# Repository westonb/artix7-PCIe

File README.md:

# artix7-PCIe
Originally designed for a SDR expansion card. Design includes breakout header, 2 general purpose buttons, and a SFP cage. 

Optimized for OSHPark 4 layer fab and home assembly. 

Design has been built but prototypes were killed by JTAG ground loop due to user error. Further work not certain, but please fork and feel free to contact for support.

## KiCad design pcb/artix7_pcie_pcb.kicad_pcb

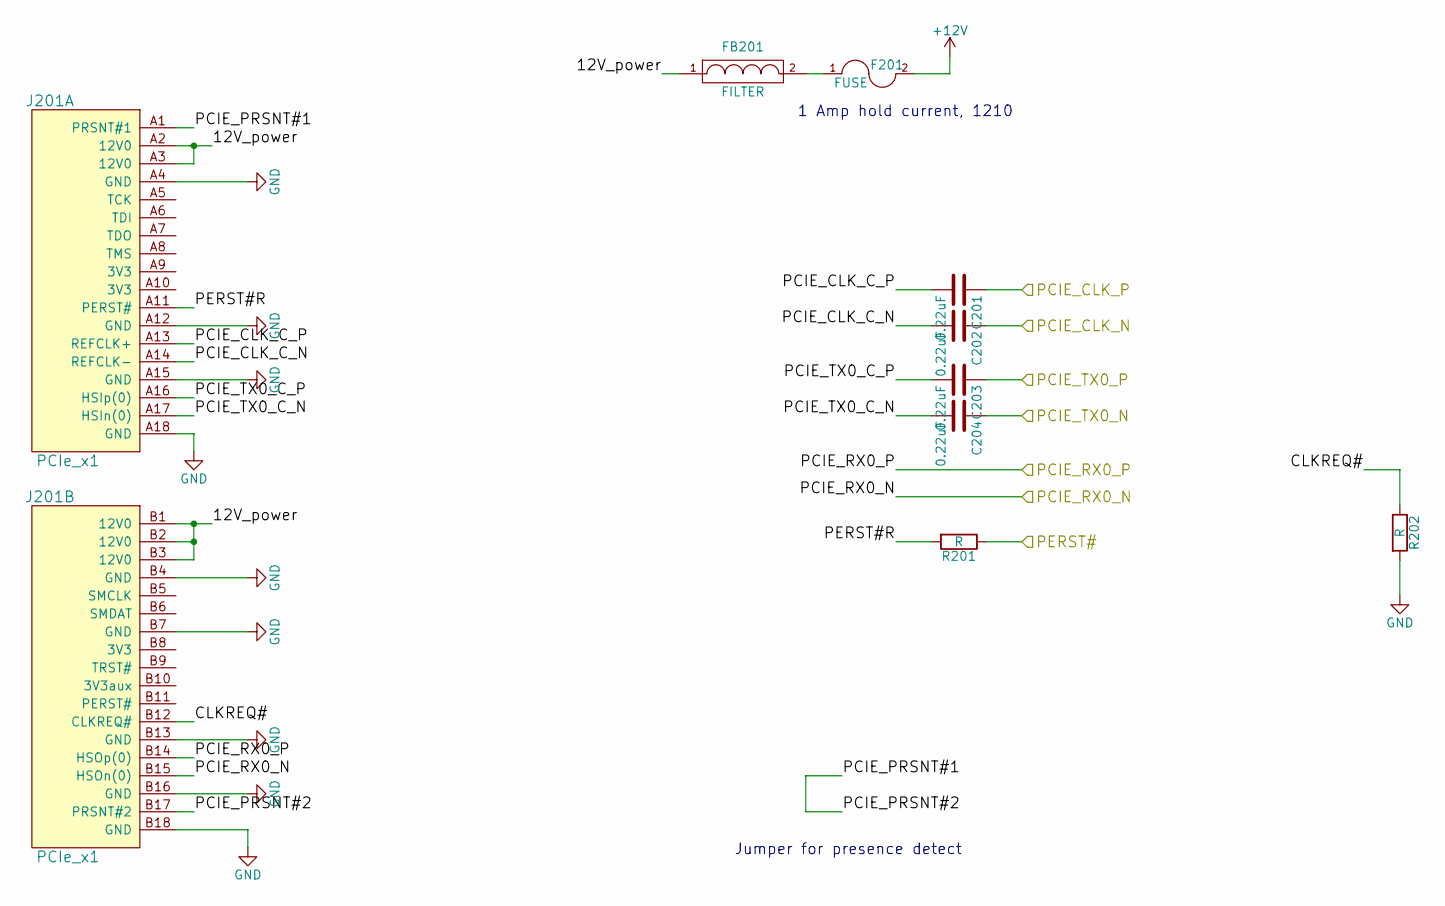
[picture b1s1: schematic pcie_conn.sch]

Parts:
C201, C202, C203, C204: 0.22uF; C_0402
F201: FUSE; SMD-0805
FB201: FILTER; L_0603
J201: PCIe_x1; PCIe_1x
R201, R202: R; R_0402

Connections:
+12V: F201.2; also elsewhere on the board
/FPGA Transceivers/PCIE_CLK_N: C202.1; also elsewhere on the board
/FPGA Transceivers/PCIE_CLK_P: C201.1; also elsewhere on the board
/FPGA Transceivers/PCIE_RX0_N: J201.B15 (HSOn(0)); also elsewhere on the board
/FPGA Transceivers/PCIE_RX0_P: J201.B14 (HSOp(0)); also elsewhere on the board
/FPGA Transceivers/PCIE_TX0_N: C204.1; also elsewhere on the board
/FPGA Transceivers/PCIE_TX0_P: C203.1; also elsewhere on the board
/PCIe Connector/12V_power: FB201.1, J201.A2 (12V0), J201.A3 (12V0), J201.B1 (12V0), J201.B2 (12V0), J201.B3 (12V0)
/PCIe Connector/CLKREQ#: J201.B12 (CLKREQ#), R202.1
/PCIe Connector/PCIE_CLK_C_N: C202.2, J201.A14 (REFCLK-)
/PCIe Connector/PCIE_CLK_C_P: C201.2, J201.A13 (REFCLK+)
/PCIe Connector/PCIE_PRSNT#1: J201.A1 (PRSNT#1), J201.B17 (PRSNT#2)
/PCIe Connector/PCIE_TX0_C_N: C204.2, J201.A17 (HSIn(0))
/PCIe Connector/PCIE_TX0_C_P: C203.2, J201.A16 (HSIp(0))
/PCIe Connector/PERST#R: J201.A11 (PERST#), R201.2
/User IO/PCIE_PERST: R201.1; also elsewhere on the board
GND: J201.A4 (GND), J201.A12 (GND), J201.A15 (GND), J201.A18 (GND), J201.B4 (GND), J201.B7 (GND), J201.B13 (GND), J201.B16 (GND), J201.B18 (GND), R202.2; also elsewhere on the board
unnamed: F201.1, FB201.2

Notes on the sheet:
Jumper for presence detect
1 Amp hold current, 1210

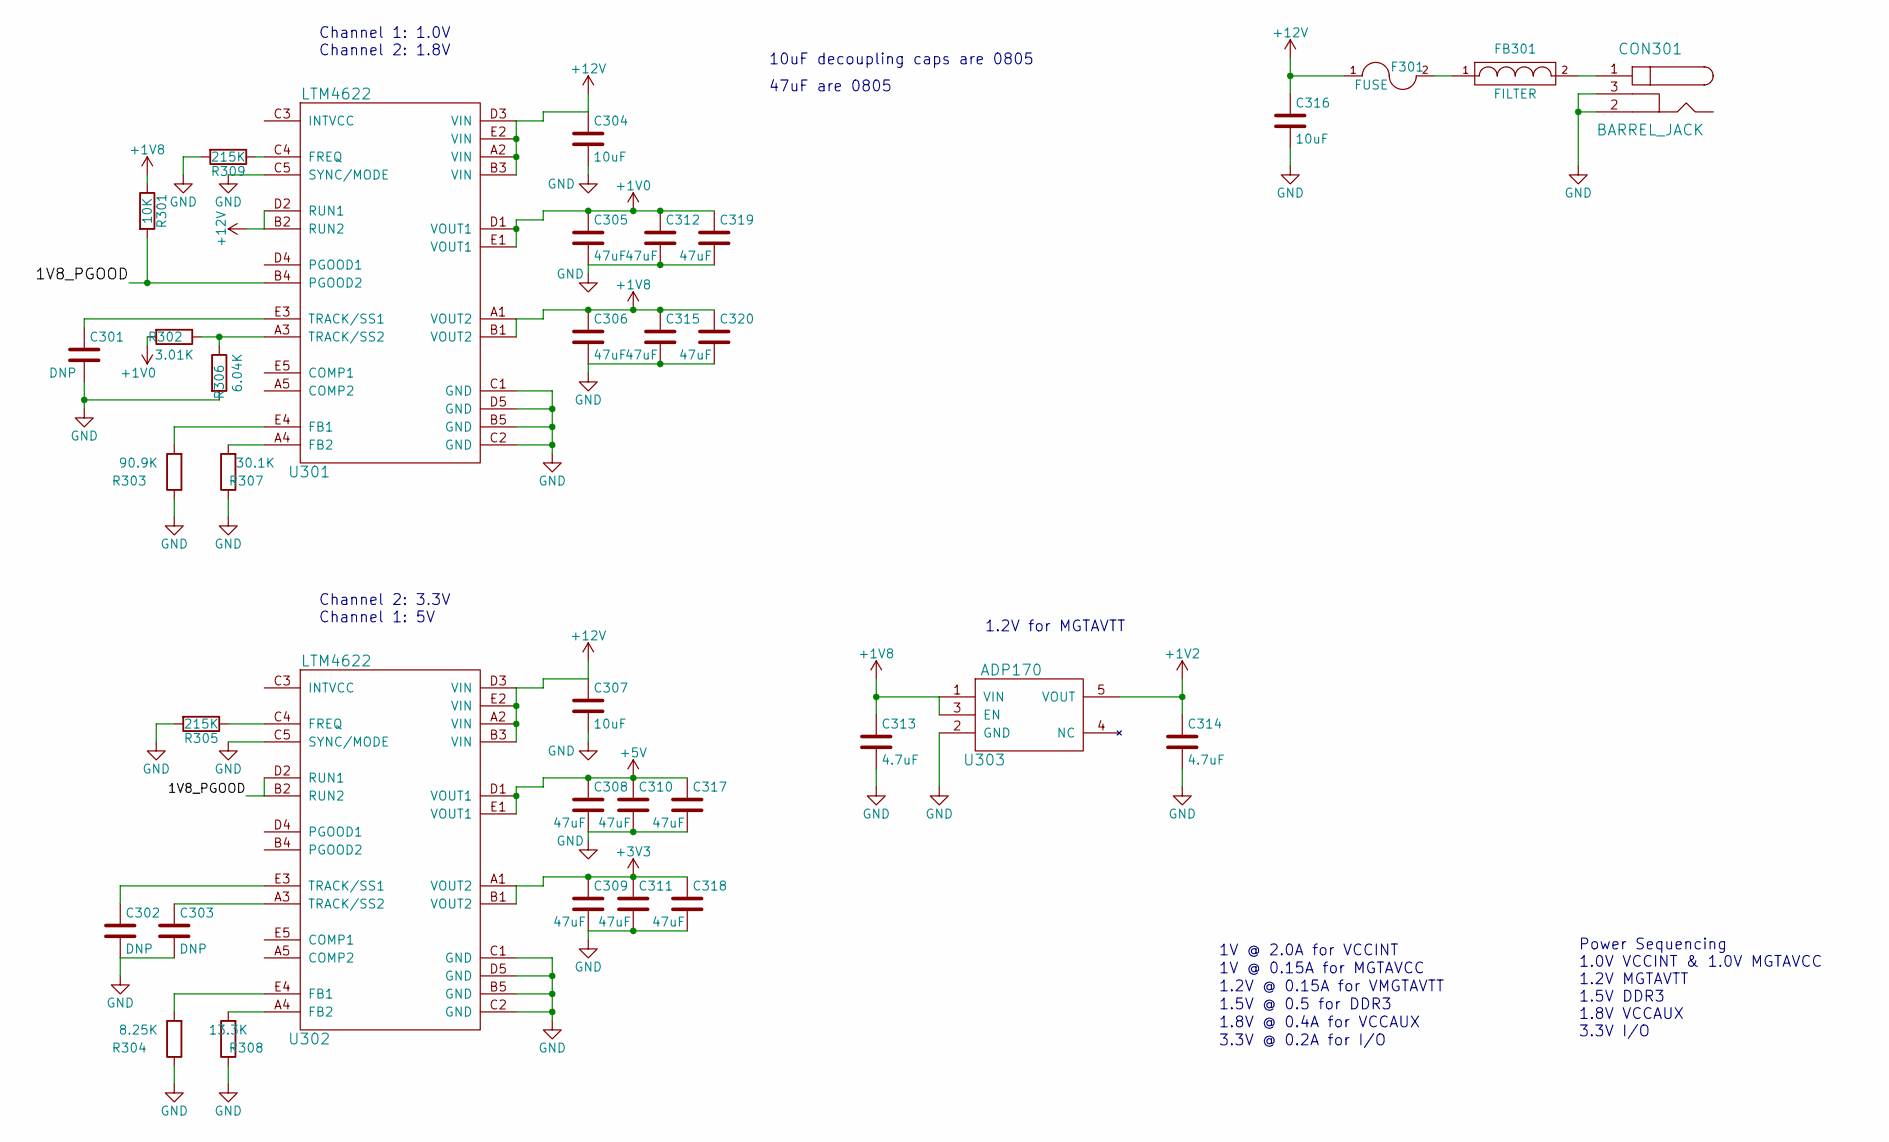
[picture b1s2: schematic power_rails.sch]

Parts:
C301, C302, C303: DNP; C_0402
C304, C307, C316: 10uF; C_0805
C305, C306, C308, C309, C310, C311, C312, C315, C317, C318, C319, C320: 47uF; C_0805
C313, C314: 4.7uF; C_0402
CON301: BARREL_JACK; DC_2.1mm_PJ-202A
F301: FUSE; SMD-0805
FB301: FILTER; L_0603
R301: 10K; R_0402
R302: 3.01K; R_0402
R303: 90.9K; R_0402
R304: 8.25K; R_0402
R305, R309: 215K; R_0402
R306: 6.04K; R_0402
R307: 30.1K; R_0402
R308: 13.3K; R_0402
U301, U302: LTM4622; LGA25_6_25x6_25
U303: ADP170; TSOT-23-5

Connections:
+1V0: C305.1, C312.1, C319.1, R302.2, U301.D1 (VOUT1), U301.E1 (VOUT1); also elsewhere on the board
+1V2: C314.1, U303.5 (VOUT); also elsewhere on the board
+1V8: C306.1, C313.1, C315.1, C320.1, R301.1, U301.A1 (VOUT2), U301.B1 (VOUT2), U303.1 (VIN), U303.3 (EN); also elsewhere on the board
+3V3: C309.1, C311.1, C318.1, U302.A1 (VOUT2), U302.B1 (VOUT2); also elsewhere on the board
+5V: C308.1, C310.1, C317.1, U302.D1 (VOUT1), U302.E1 (VOUT1); also elsewhere on the board
+12V: C304.1, C307.1, C316.1, F301.1, U301.A2 (VIN), U301.B2 (RUN2), U301.B3 (VIN), U301.D2 (RUN1), U301.D3 (VIN), U301.E2 (VIN), U302.A2 (VIN), U302.B3 (VIN), U302.D3 (VIN), U302.E2 (VIN); also elsewhere on the board
/Power Rails/1V8_PGOOD: R301.2, U301.B4 (PGOOD2), U302.B2 (RUN2), U302.D2 (RUN1)
GND: C301.2, C302.2, C303.2, C304.2, C305.2, C306.2, C307.2, C308.2, C309.2, C310.2, C311.2, C312.2, C313.2, C314.2, C315.2, C316.2, C317.2, C318.2, C319.2, C320.2, CON301.2, CON301.3, R303.1, R304.1, R305.2, R306.2, R307.1, R308.1, R309.2, U301.B5 (GND), U301.C1 (GND), U301.C2 (GND), U301.C5 (SYNC/MODE), U301.D5 (GND), U302.B5 (GND), U302.C1 (GND), U302.C2 (GND), U302.C5 (SYNC/MODE), U302.D5 (GND), U303.2 (GND); also elsewhere on the board
unnamed: C301.1, U301.E3 (TRACK/SS1)
unnamed: C302.1, U302.E3 (TRACK/SS1)
unnamed: C303.1, U302.A3 (TRACK/SS2)
unnamed: CON301.1, FB301.2
unnamed: F301.2, FB301.1
unnamed: R302.1, R306.1, U301.A3 (TRACK/SS2)
unnamed: R303.2, U301.E4 (FB1)
unnamed: R304.2, U302.E4 (FB1)
unnamed: R305.1, U302.C4 (FREQ)
unnamed: R307.2, U301.A4 (FB2)
unnamed: R308.2, U302.A4 (FB2)
unnamed: R309.1, U301.C4 (FREQ)

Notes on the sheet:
1.5V @ 0.5 for DDR3
1V @ 2.0A for VCCINT
1.2V @ 0.15A for VMGTAVTT
1.8V @ 0.4A for VCCAUX
3.3V @ 0.2A for I/O
1V @ 0.15A for MGTAVCC
Power Sequencing 1.0V VCCINT & 1.0V MGTAVCC 1.2V MGTAVTT 1.5V DDR3 1.8V VCCAUX 3.3V I/O
Channel 1: 1.0V Channel 2: 1.8V
1.2V for MGTAVTT
Channel 2: 3.3V Channel 1: 5V
10uF decoupling caps are 0805
47uF are 0805

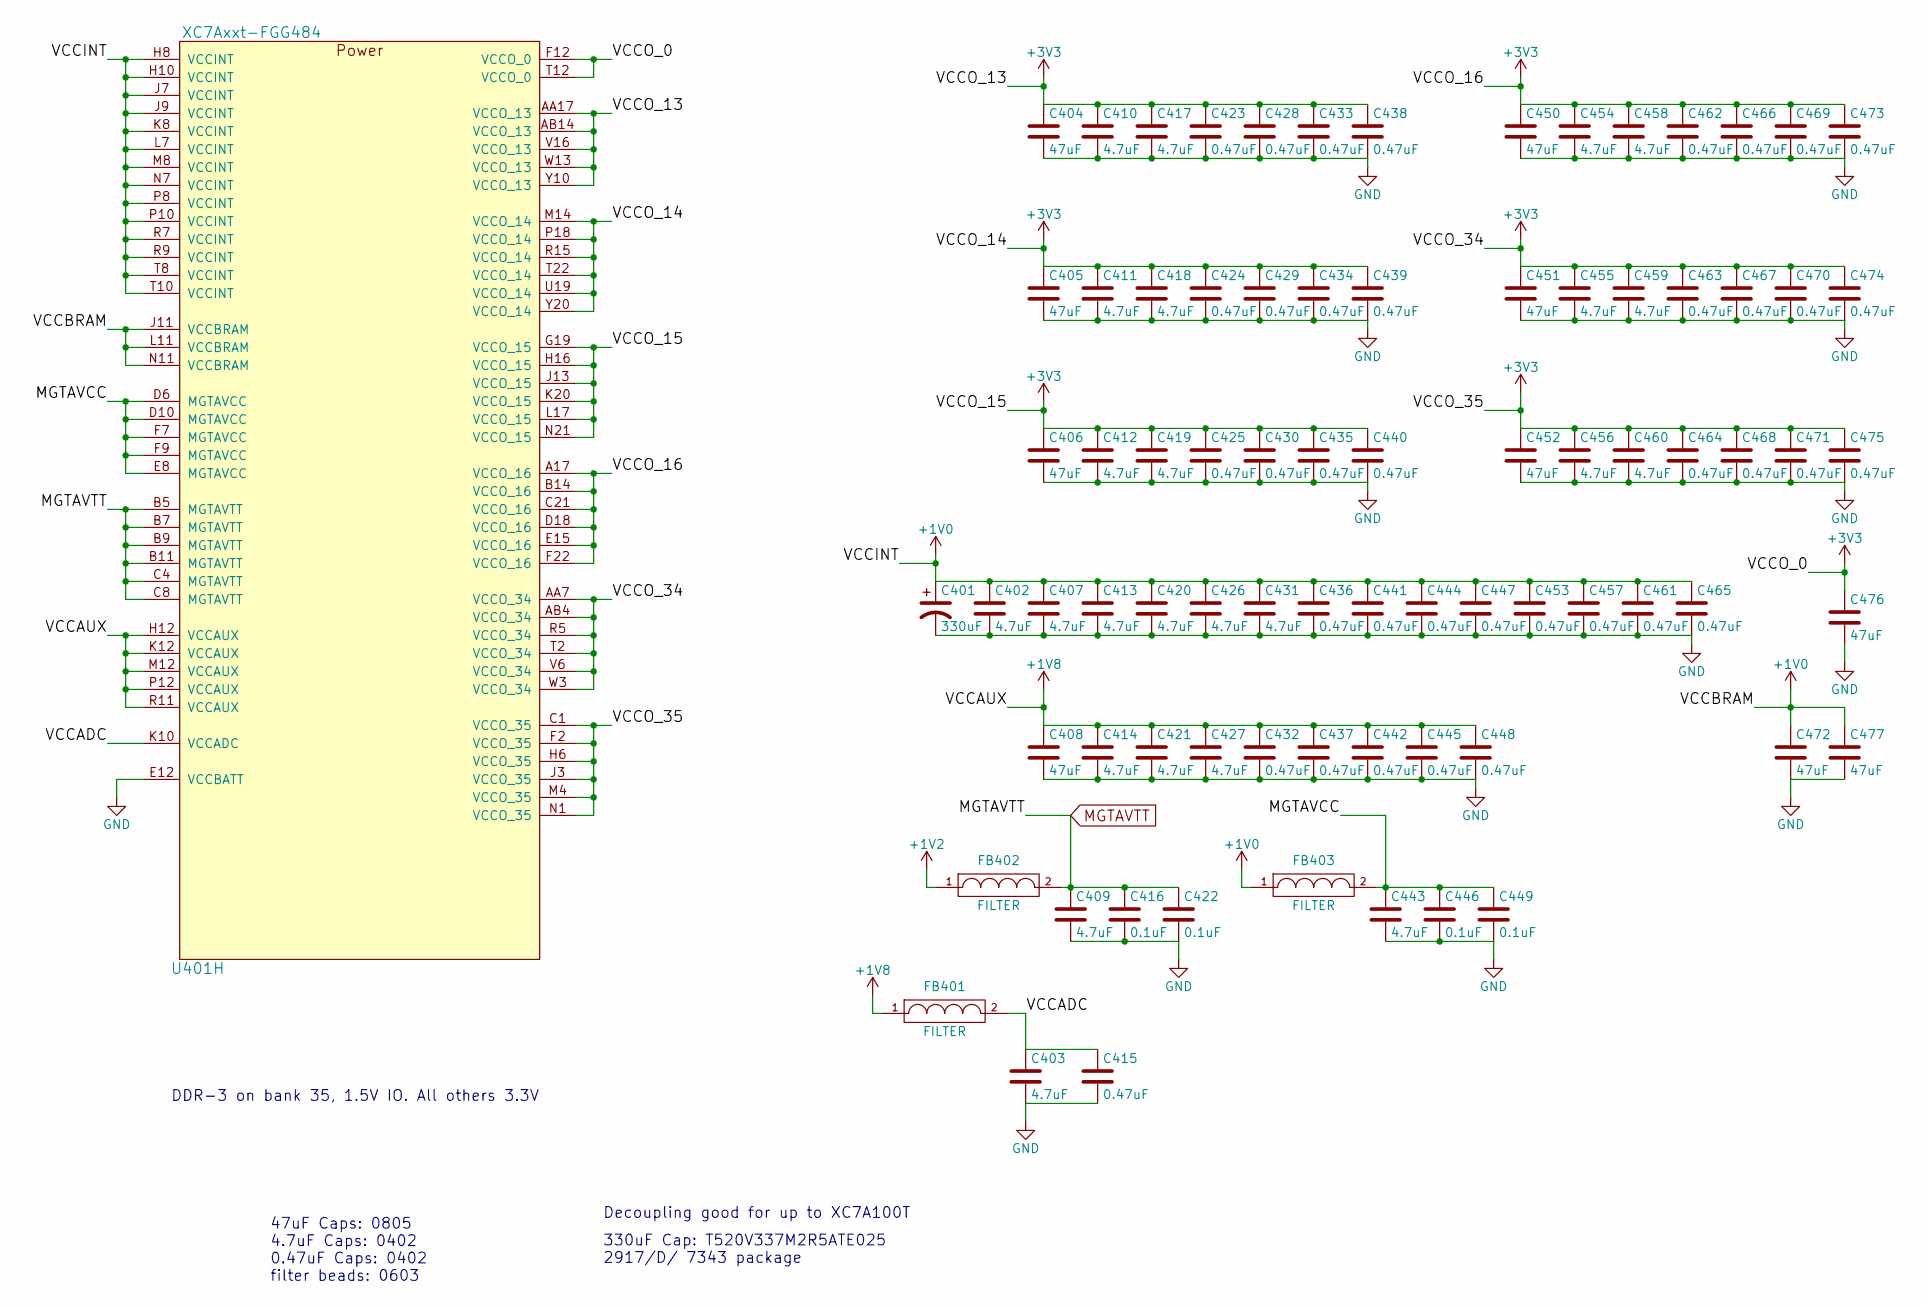
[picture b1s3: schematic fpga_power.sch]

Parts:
C401: 330uF; TantalC_SizeD_EIA-7343
C402, C403, C407, C409, C410, C411, C412, C413, C414, C417, C418, C419, C420, C421, C426, C427, C431, C443, C454, C455, C456, C458, C459, C460: 4.7uF; 0402_in_grid
C404, C405, C406, C408, C450, C451, C452, C472, C476, C477: 47uF; C_0805
C415, C423, C424, C425, C428, C429, C430, C432, C433, C434, C435, C436, C437, C438, C439, C440, C441, C442, C444, C445, C447, C448, C453, C457, C461, C462, C463, C464, C465, C466, C467, C468, C469, C470, C471, C473, C474, C475: 0.47uF; 0402_in_grid
C416, C422, C446, C449: 0.1uF; 0402_in_grid
FB401, FB402, FB403: FILTER; L_0603
U401: XC7Axxt-FGG484; BGA_484_22x22_FULLARRAY_1MM

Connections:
+1V0: C401.1, C402.1, C407.1, C413.1, C420.1, C426.1, C431.1, C436.1, C441.1, C444.1, C447.1, C453.1, C457.1, C461.1, C465.1, C472.1, C477.1, FB403.1, U401.H8 (VCCINT), U401.H10 (VCCINT), U401.J7 (VCCINT), U401.J9 (VCCINT), U401.J11 (VCCBRAM), U401.K8 (VCCINT), U401.L7 (VCCINT), U401.L11 (VCCBRAM), U401.M8 (VCCINT), U401.N7 (VCCINT), U401.N11 (VCCBRAM), U401.P8 (VCCINT), U401.P10 (VCCINT), U401.R7 (VCCINT), U401.R9 (VCCINT), U401.T8 (VCCINT), U401.T10 (VCCINT); also elsewhere on the board
+1V2: FB402.1; also elsewhere on the board
+1V8: C408.1, C414.1, C421.1, C427.1, C432.1, C437.1, C442.1, C445.1, C448.1, FB401.1, U401.H12 (VCCAUX), U401.K12 (VCCAUX), U401.M12 (VCCAUX), U401.P12 (VCCAUX), U401.R11 (VCCAUX); also elsewhere on the board
+3V3: C404.1, C405.1, C406.1, C410.1, C411.1, C412.1, C417.1, C418.1, C419.1, C423.1, C424.1, C425.1, C428.1, C429.1, C430.1, C433.1, C434.1, C435.1, C438.1, C439.1, C440.1, C450.1, C451.1, C452.1, C454.1, C455.1, C456.1, C458.1, C459.1, C460.1, C462.1, C463.1, C464.1, C466.1, C467.1, C468.1, C469.1, C470.1, C471.1, C473.1, C474.1, C475.1, C476.1, U401.A17 (VCCO_16), U401.AA7 (VCCO_34), U401.AA17 (VCCO_13), U401.AB4 (VCCO_34), U401.AB14 (VCCO_13), U401.B14 (VCCO_16), U401.C1 (VCCO_35), U401.C21 (VCCO_16), U401.D18 (VCCO_16), U401.E15 (VCCO_16), U401.F2 (VCCO_35), U401.F12 (VCCO_0), U401.F22 (VCCO_16), U401.G19 (VCCO_15), U401.H6 (VCCO_35), U401.H16 (VCCO_15), U401.J3 (VCCO_35), U401.J13 (VCCO_15), U401.K20 (VCCO_15), U401.L17 (VCCO_15), U401.M4 (VCCO_35), U401.M14 (VCCO_14), U401.N1 (VCCO_35), U401.N21 (VCCO_15), U401.P18 (VCCO_14), U401.R5 (VCCO_34), U401.R15 (VCCO_14), U401.T2 (VCCO_34), U401.T12 (VCCO_0), U401.T22 (VCCO_14), U401.U19 (VCCO_14), U401.V6 (VCCO_34), U401.V16 (VCCO_13), U401.W3 (VCCO_34), U401.W13 (VCCO_13), U401.Y10 (VCCO_13), U401.Y20 (VCCO_14); also elsewhere on the board
/FPGA Power/MGTAVCC: C443.1, C446.1, C449.1, FB403.2, U401.D6 (MGTAVCC), U401.D10 (MGTAVCC), U401.E8 (MGTAVCC), U401.F7 (MGTAVCC), U401.F9 (MGTAVCC)
/FPGA Power/VCCADC: C403.1, C415.1, FB401.2, U401.K10 (VCCADC)
GND: C401.2, C402.2, C403.2, C404.2, C405.2, C406.2, C407.2, C408.2, C409.2, C410.2, C411.2, C412.2, C413.2, C414.2, C415.2, C416.2, C417.2, C418.2, C419.2, C420.2, C421.2, C422.2, C423.2, C424.2, C425.2, C426.2, C427.2, C428.2, C429.2, C430.2, C431.2, C432.2, C433.2, C434.2, C435.2, C436.2, C437.2, C438.2, C439.2, C440.2, C441.2, C442.2, C443.2, C444.2, C445.2, C446.2, C447.2, C448.2, C449.2, C450.2, C451.2, C452.2, C453.2, C454.2, C455.2, C456.2, C457.2, C458.2, C459.2, C460.2, C461.2, C462.2, C463.2, C464.2, C465.2, C466.2, C467.2, C468.2, C469.2, C470.2, C471.2, C472.2, C473.2, C474.2, C475.2, C476.2, C477.2, U401.E12 (VCCBATT); also elsewhere on the board
MGTAVTT: C409.1, C416.1, C422.1, FB402.2, U401.B5 (MGTAVTT), U401.B7 (MGTAVTT), U401.B9 (MGTAVTT), U401.B11 (MGTAVTT), U401.C4 (MGTAVTT), U401.C8 (MGTAVTT); also elsewhere on the board

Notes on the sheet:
DDR-3 on bank 35, 1.5V IO. All others 3.3V
47uF Caps: 0805 4.7uF Caps: 0402 0.47uF Caps: 0402 filter beads: 0603
Decoupling good for up to XC7A100T
330uF Cap: T520V337M2R5ATE025 2917/D/ 7343 package

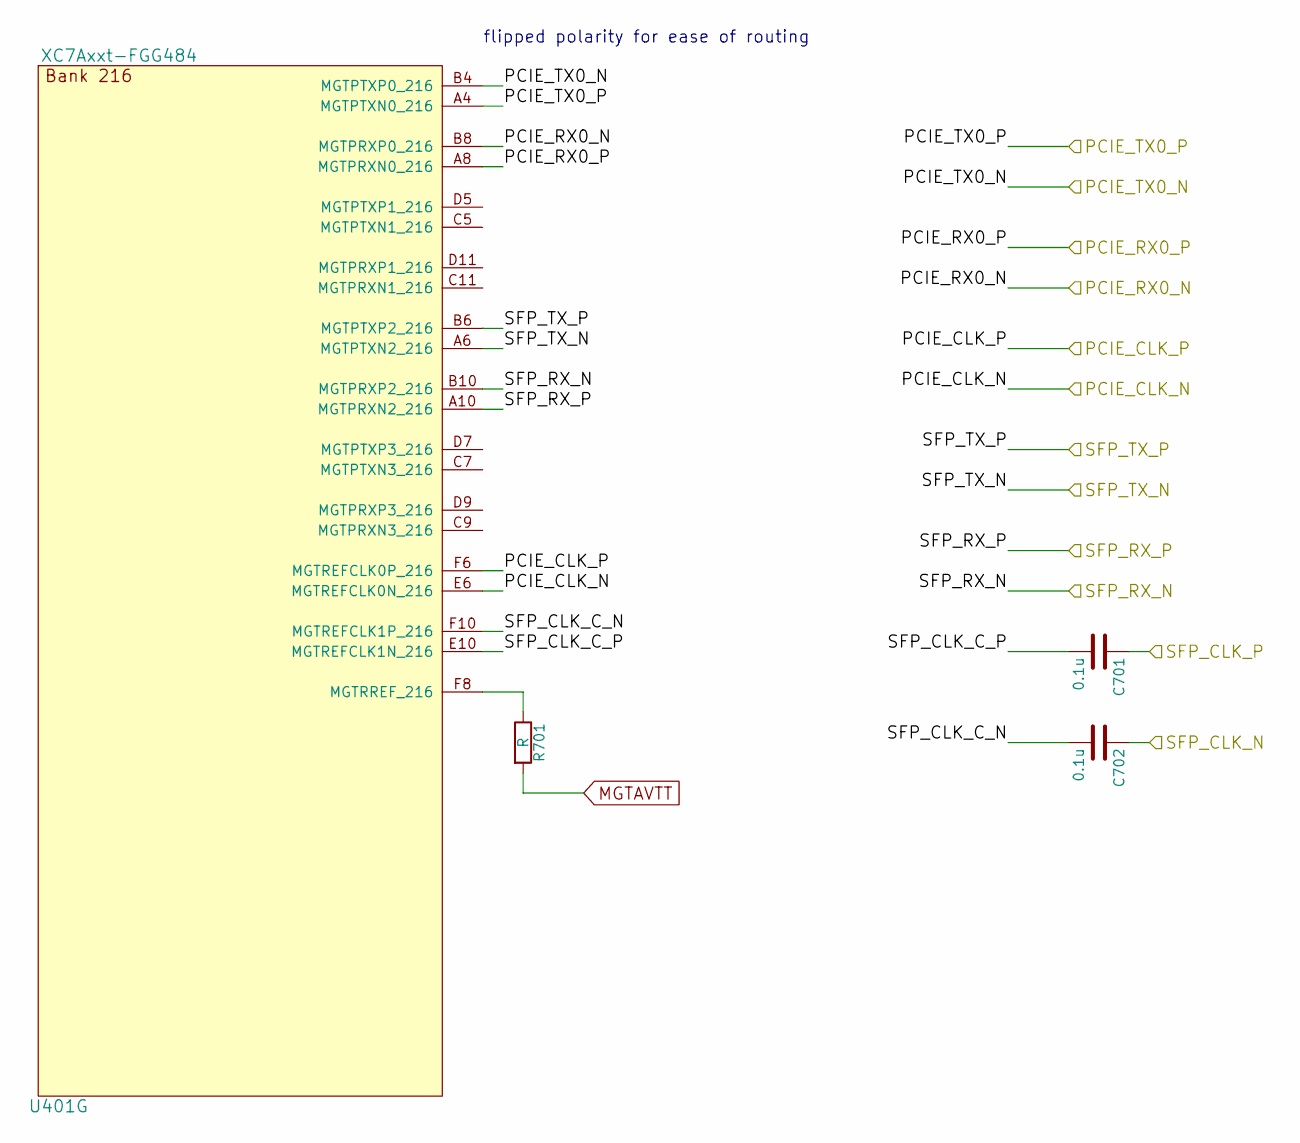
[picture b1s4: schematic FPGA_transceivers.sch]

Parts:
C701, C702: 0.1u; C_0402
R701: R; R_0402
U401: XC7Axxt-FGG484; BGA_484_22x22_FULLARRAY_1MM

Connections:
/Clocking/GTP_CLK_N: C702.1; also elsewhere on the board
/Clocking/GTP_CLK_P: C701.1; also elsewhere on the board
/FPGA Transceivers/PCIE_CLK_N: U401.E6 (MGTREFCLK0N_216); also elsewhere on the board
/FPGA Transceivers/PCIE_CLK_P: U401.F6 (MGTREFCLK0P_216); also elsewhere on the board
/FPGA Transceivers/PCIE_RX0_N: U401.B8 (MGTPRXP0_216); also elsewhere on the board
/FPGA Transceivers/PCIE_RX0_P: U401.A8 (MGTPRXN0_216); also elsewhere on the board
/FPGA Transceivers/PCIE_TX0_N: U401.B4 (MGTPTXP0_216); also elsewhere on the board
/FPGA Transceivers/PCIE_TX0_P: U401.A4 (MGTPTXN0_216); also elsewhere on the board
/FPGA Transceivers/SFP_CLK_C_N: C702.2, U401.F10 (MGTREFCLK1P_216)
/FPGA Transceivers/SFP_CLK_C_P: C701.2, U401.E10 (MGTREFCLK1N_216)
/FPGA Transceivers/SFP_RX_N: U401.B10 (MGTPRXP2_216); also elsewhere on the board
/FPGA Transceivers/SFP_RX_P: U401.A10 (MGTPRXN2_216); also elsewhere on the board
/FPGA Transceivers/SFP_TX_N: U401.A6 (MGTPTXN2_216); also elsewhere on the board
/FPGA Transceivers/SFP_TX_P: U401.B6 (MGTPTXP2_216); also elsewhere on the board
MGTAVTT: R701.2; also elsewhere on the board
unnamed: R701.1, U401.F8 (MGTRREF_216)

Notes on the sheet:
flipped polarity for ease of routing

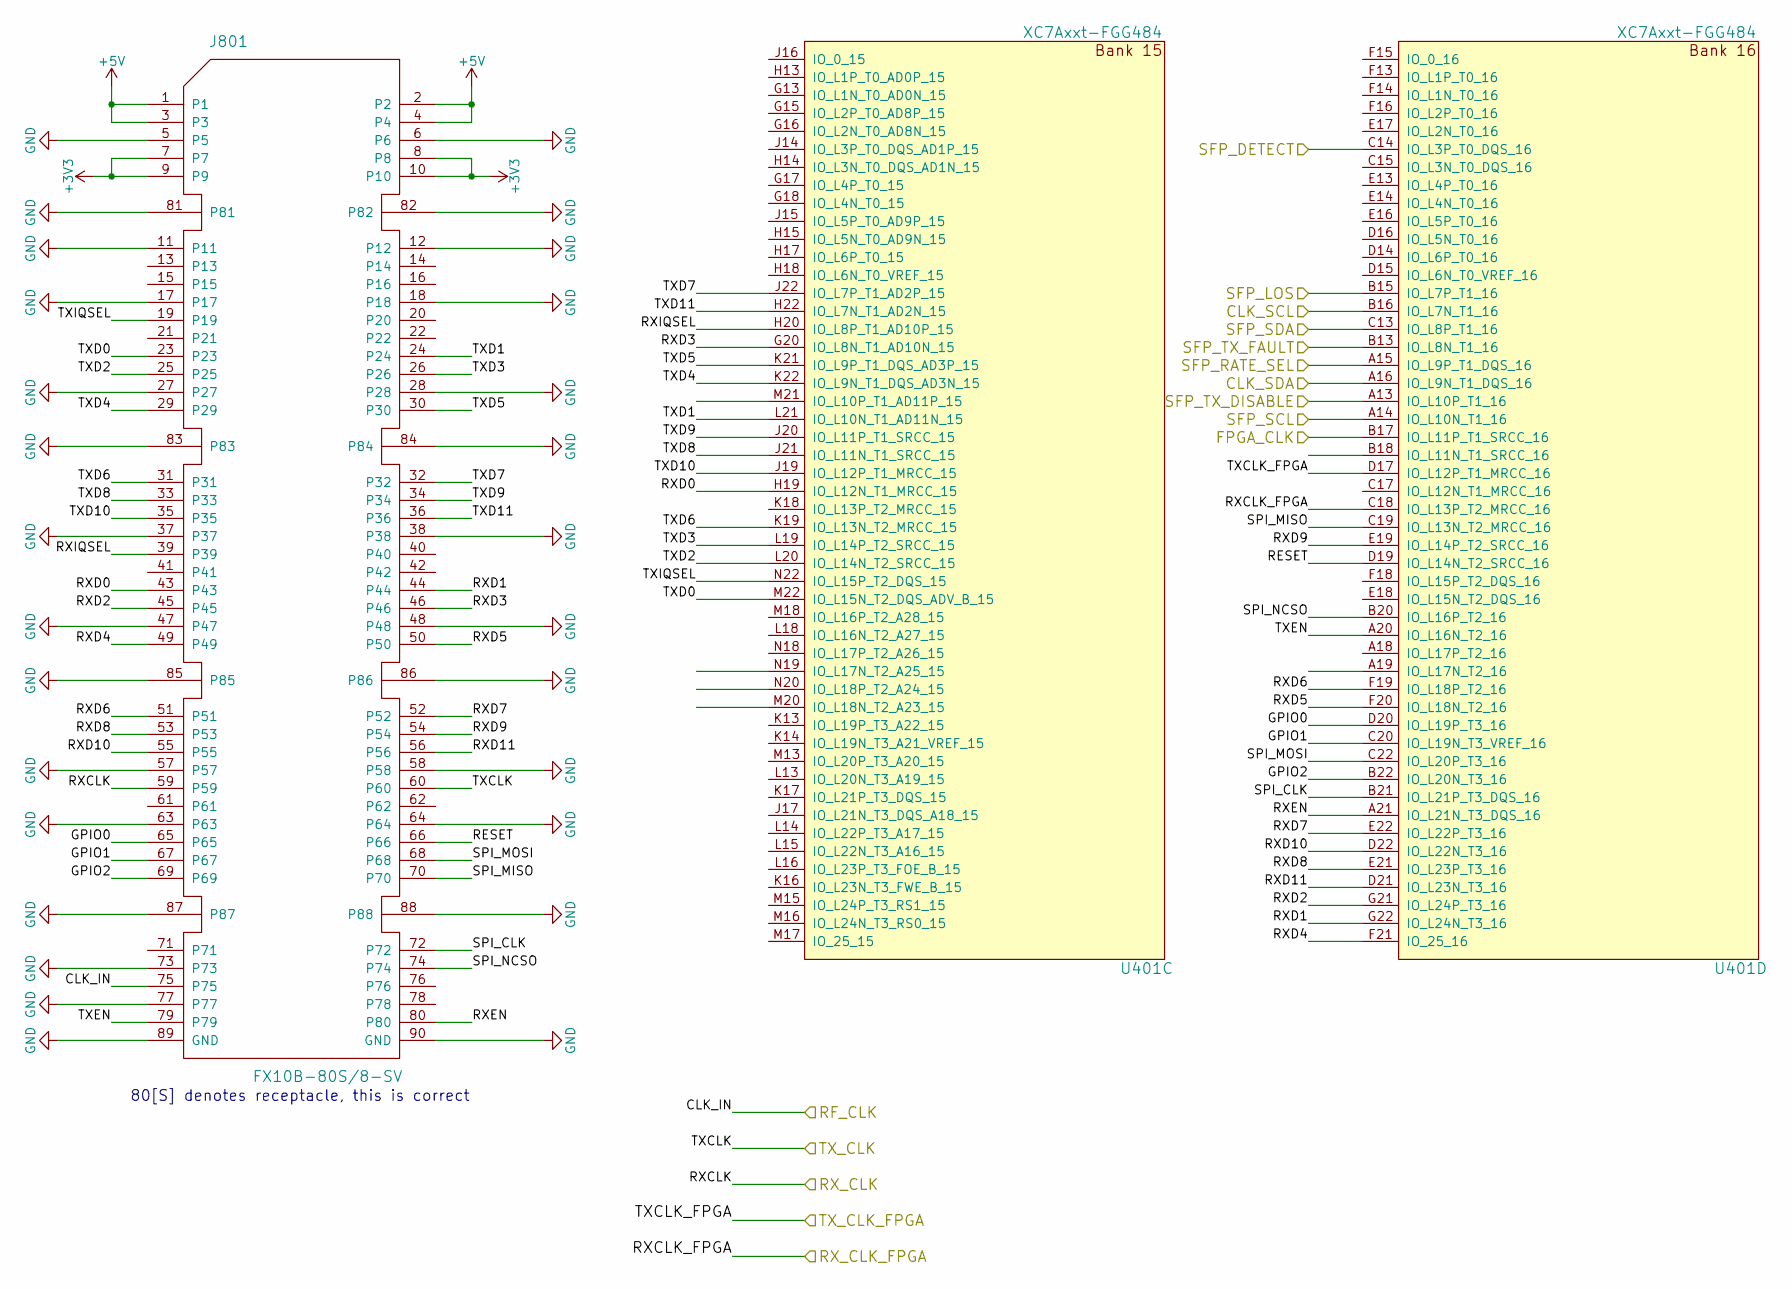
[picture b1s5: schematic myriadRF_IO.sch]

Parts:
J801: FX10B-80S/8-SV; FX10B_80S_8_SV
U401: XC7Axxt-FGG484; BGA_484_22x22_FULLARRAY_1MM

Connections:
+3V3: J801.7, J801.8, J801.9, J801.10; also elsewhere on the board
+5V: J801.1, J801.2, J801.3, J801.4; also elsewhere on the board
/Clocking/CLK_SCL: U401.B16 (IO_L7N_T1_16); also elsewhere on the board
/Clocking/CLK_SDA: U401.A16 (IO_L9N_T1_DQS_16); also elsewhere on the board
/Clocking/FPGA_CLK: U401.B17 (IO_L11P_T1_SRCC_16); also elsewhere on the board
/Clocking/RF_CLK: J801.75; also elsewhere on the board
/Clocking/RX_CLK: J801.59; also elsewhere on the board
/Clocking/RX_CLK_FPGA: U401.C18 (IO_L13P_T2_MRCC_16); also elsewhere on the board
/Clocking/TX_CLK: J801.60; also elsewhere on the board
/Clocking/TX_CLK_FPGA: U401.D17 (IO_L12P_T1_MRCC_16); also elsewhere on the board
/MyriadRF IO/GPIO0: J801.65, U401.D20 (IO_L19P_T3_16)
/MyriadRF IO/GPIO1: J801.67, U401.C20 (IO_L19N_T3_VREF_16)
/MyriadRF IO/GPIO2: J801.69, U401.B22 (IO_L20N_T3_16)
/MyriadRF IO/RESET: J801.66, U401.D19 (IO_L14N_T2_SRCC_16)
/MyriadRF IO/RXD0: J801.43, U401.H19 (IO_L12N_T1_MRCC_15)
/MyriadRF IO/RXD1: J801.44, U401.G22 (IO_L24N_T3_16)
/MyriadRF IO/RXD2: J801.45, U401.G21 (IO_L24P_T3_16)
/MyriadRF IO/RXD3: J801.46, U401.G20 (IO_L8N_T1_AD10N_15)
/MyriadRF IO/RXD4: J801.49, U401.F21 (IO_25_16)
/MyriadRF IO/RXD5: J801.50, U401.F20 (IO_L18N_T2_16)
/MyriadRF IO/RXD6: J801.51, U401.F19 (IO_L18P_T2_16)
/MyriadRF IO/RXD7: J801.52, U401.E22 (IO_L22P_T3_16)
/MyriadRF IO/RXD8: J801.53, U401.E21 (IO_L23P_T3_16)
/MyriadRF IO/RXD9: J801.54, U401.E19 (IO_L14P_T2_SRCC_16)
/MyriadRF IO/RXD10: J801.55, U401.D22 (IO_L22N_T3_16)
/MyriadRF IO/RXD11: J801.56, U401.D21 (IO_L23N_T3_16)
/MyriadRF IO/RXEN: J801.80, U401.A21 (IO_L21N_T3_DQS_16)
/MyriadRF IO/RXIQSEL: J801.39, U401.H20 (IO_L8P_T1_AD10P_15)
/MyriadRF IO/SFP_DETECT: U401.C14 (IO_L3P_T0_DQS_16); also elsewhere on the board
/MyriadRF IO/SFP_RATE_SEL: U401.A15 (IO_L9P_T1_DQS_16); also elsewhere on the board
/MyriadRF IO/SFP_SCL: U401.A14 (IO_L10N_T1_16); also elsewhere on the board
/MyriadRF IO/SFP_SDA: U401.C13 (IO_L8P_T1_16); also elsewhere on the board
/MyriadRF IO/SFP_TX_DISABLE: U401.A13 (IO_L10P_T1_16); also elsewhere on the board
/MyriadRF IO/SFP_TX_FAULT: U401.B13 (IO_L8N_T1_16); also elsewhere on the board
/MyriadRF IO/SPI_CLK: J801.72, U401.B21 (IO_L21P_T3_DQS_16)
/MyriadRF IO/SPI_MISO: J801.70, U401.C19 (IO_L13N_T2_MRCC_16)
/MyriadRF IO/SPI_MOSI: J801.68, U401.C22 (IO_L20P_T3_16)
/MyriadRF IO/SPI_NCSO: J801.74, U401.B20 (IO_L16P_T2_16)
/MyriadRF IO/TXD0: J801.23, U401.M22 (IO_L15N_T2_DQS_ADV_B_15)
/MyriadRF IO/TXD1: J801.24, U401.L21 (IO_L10N_T1_AD11N_15)
/MyriadRF IO/TXD2: J801.25, U401.L20 (IO_L14N_T2_SRCC_15)
/MyriadRF IO/TXD3: J801.26, U401.L19 (IO_L14P_T2_SRCC_15)
/MyriadRF IO/TXD4: J801.29, U401.K22 (IO_L9N_T1_DQS_AD3N_15)
/MyriadRF IO/TXD5: J801.30, U401.K21 (IO_L9P_T1_DQS_AD3P_15)
/MyriadRF IO/TXD6: J801.31, U401.K19 (IO_L13N_T2_MRCC_15)
/MyriadRF IO/TXD7: J801.32, U401.J22 (IO_L7P_T1_AD2P_15)
/MyriadRF IO/TXD8: J801.33, U401.J21 (IO_L11N_T1_SRCC_15)
/MyriadRF IO/TXD9: J801.34, U401.J20 (IO_L11P_T1_SRCC_15)
/MyriadRF IO/TXD10: J801.35, U401.J19 (IO_L12P_T1_MRCC_15)
/MyriadRF IO/TXD11: J801.36, U401.H22 (IO_L7N_T1_AD2N_15)
/MyriadRF IO/TXEN: J801.79, U401.A20 (IO_L16N_T2_16)
/MyriadRF IO/TXIQSEL: J801.19, U401.N22 (IO_L15P_T2_DQS_15)
/SFP/LOS: U401.B15 (IO_L7P_T1_16); also elsewhere on the board
GND: J801.5, J801.6, J801.11, J801.12, J801.17, J801.18, J801.27, J801.28, J801.37, J801.38, J801.47, J801.48, J801.57, J801.58, J801.63, J801.64, J801.73, J801.77, J801.81, J801.82, J801.83, J801.84, J801.85, J801.86, J801.87, J801.88, J801.89 (GND), J801.90 (GND); also elsewhere on the board

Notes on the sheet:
80[S] denotes receptacle, this is correct

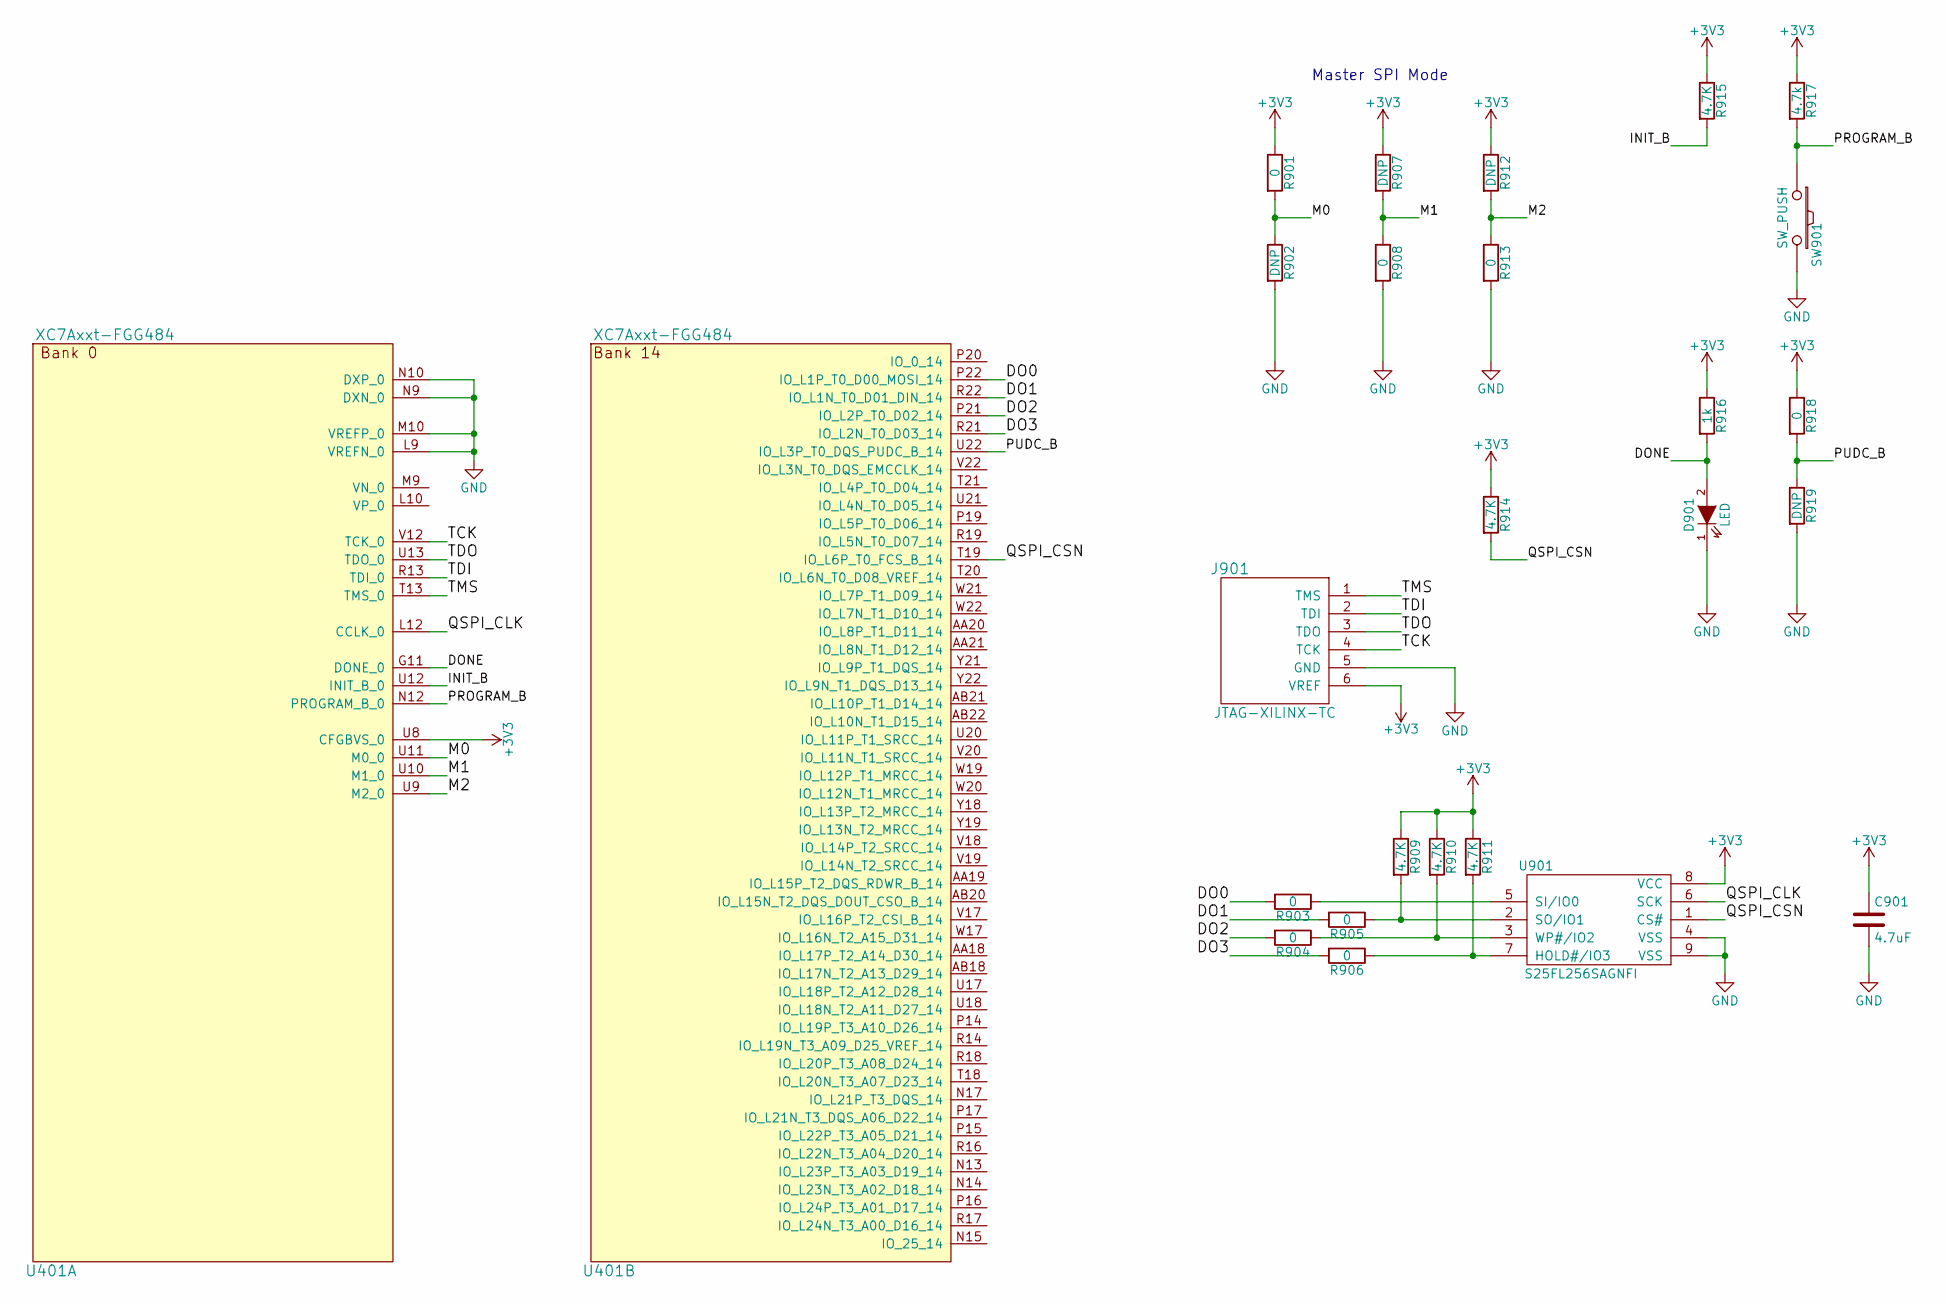
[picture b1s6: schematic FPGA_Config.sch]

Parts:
C901: 4.7uF; C_0402
D901: LED; LED-0805
J901: JTAG-XILINX-TC; TC2030-IDC-NL
R901, R903, R904, R905, R906, R908, R913, R918: 0; R_0402
R902, R907, R912, R919: DNP; R_0402
R909, R910, R911, R914, R915: 4.7K; R_0402
R916: 1k; R_0402
R917: 4.7k; R_0402
SW901: SW_PUSH; button-5mm
U401: XC7Axxt-FGG484; BGA_484_22x22_FULLARRAY_1MM
U901: S25FL256SAGNFI; 8-WSON_6x8_1.27mm

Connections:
+3V3: C901.1, J901.6 (VREF), R901.1, R907.1, R909.1, R910.1, R911.1, R912.1, R914.1, R915.1, R916.1, R917.1, R918.1, U401.U8 (CFGBVS_0), U901.8 (VCC); also elsewhere on the board
/FPGA Config/DO0: R903.2, U401.P22 (IO_L1P_T0_D00_MOSI_14)
/FPGA Config/DO1: R905.2, U401.R22 (IO_L1N_T0_D01_DIN_14)
/FPGA Config/DO2: R904.2, U401.P21 (IO_L2P_T0_D02_14)
/FPGA Config/DO3: R906.2, U401.R21 (IO_L2N_T0_D03_14)
/FPGA Config/DONE: D901.2 (A), R916.2, U401.G11 (DONE_0)
/FPGA Config/INIT_B: R915.2, U401.U12 (INIT_B_0)
/FPGA Config/M0: R901.2, R902.1, U401.U11 (M0_0)
/FPGA Config/M1: R907.2, R908.1, U401.U10 (M1_0)
/FPGA Config/M2: R912.2, R913.1, U401.U9 (M2_0)
/FPGA Config/PROGRAM_B: R917.2, SW901.1, U401.N12 (PROGRAM_B_0)
/FPGA Config/PUDC_B: R918.2, R919.1, U401.U22 (IO_L3P_T0_DQS_PUDC_B_14)
/FPGA Config/QSPI_CLK: U401.L12 (CCLK_0), U901.6 (SCK)
/FPGA Config/QSPI_CSN: R914.2, U401.T19 (IO_L6P_T0_FCS_B_14), U901.1 (CS#)
/FPGA Config/TCK: J901.4 (TCK), U401.V12 (TCK_0)
/FPGA Config/TDI: J901.2 (TDI), U401.R13 (TDI_0)
/FPGA Config/TDO: J901.3 (TDO), U401.U13 (TDO_0)
/FPGA Config/TMS: J901.1 (TMS), U401.T13 (TMS_0)
GND: C901.2, D901.1 (K), J901.5 (GND), R902.2, R908.2, R913.2, R919.2, SW901.2, U401.L9 (VREFN_0), U401.M10 (VREFP_0), U401.N9 (DXN_0), U401.N10 (DXP_0), U901.4 (VSS), U901.9 (VSS); also elsewhere on the board
unnamed: R903.1, U901.5 (SI/IO0)
unnamed: R904.1, R910.2, U901.3 (WP#/IO2)
unnamed: R905.1, R909.2, U901.2 (SO/IO1)
unnamed: R906.1, R911.2, U901.7 (HOLD#/IO3)

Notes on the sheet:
Master SPI Mode
